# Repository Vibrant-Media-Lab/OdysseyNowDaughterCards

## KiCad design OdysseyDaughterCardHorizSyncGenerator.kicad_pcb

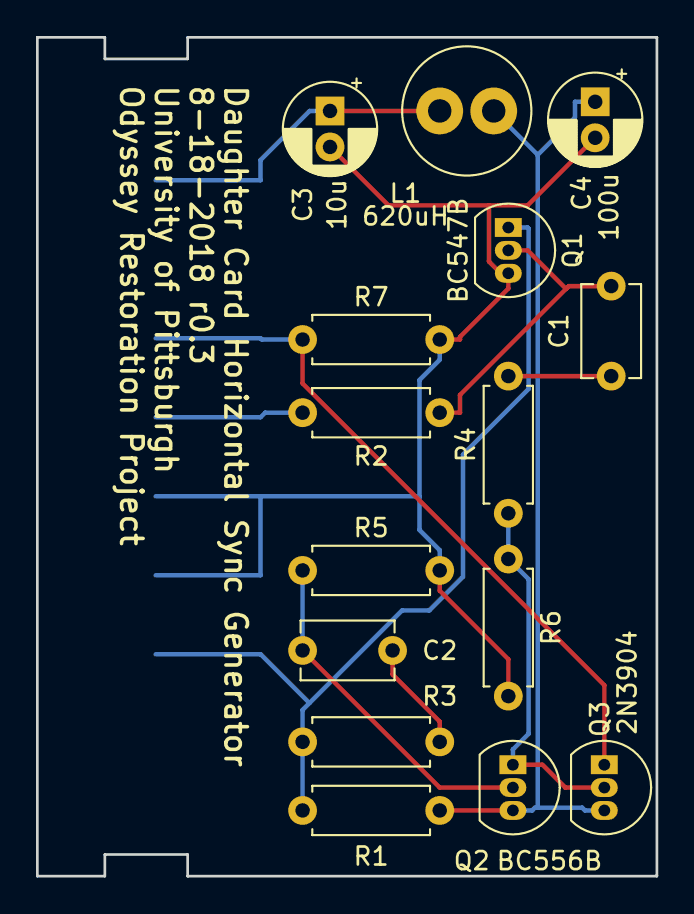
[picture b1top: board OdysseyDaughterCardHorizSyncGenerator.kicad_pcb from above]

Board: 2 copper layers, 34.4 x 46.6 mm, 16 parts (0 on the bottom side), 11 nets.

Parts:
C1: 470p; C_Disc_D5.1mm_W3.2mm_P5.00mm
C2: 680p; C_Disc_D5.1mm_W3.2mm_P5.00mm
C3: 10u; CP_Radial_D5.0mm_P2.00mm
C4: 100u; CP_Radial_D5.0mm_P2.00mm
L1: 620uH; L_Radial_D7.0mm_P3.00mm
Q1: BC547B; TO-92_Inline
Q2: BC556B; TO-92_Inline
Q3: 2N3904; TO-92_Inline
R1, R6: 1k; R_Axial_DIN0207_L6.3mm_D2.5mm_P7.62mm_Horizontal
R2: 150k; R_Axial_DIN0207_L6.3mm_D2.5mm_P7.62mm_Horizontal
R3: 820; R_Axial_DIN0207_L6.3mm_D2.5mm_P7.62mm_Horizontal
R4: 3.3k; R_Axial_DIN0207_L6.3mm_D2.5mm_P7.62mm_Horizontal
R5: 300k; R_Axial_DIN0207_L6.3mm_D2.5mm_P7.62mm_Horizontal
R7: 470; R_Axial_DIN0207_L6.3mm_D2.5mm_P7.62mm_Horizontal
X1: OdysseyDaughterCard; Odyssey_Daughter_Card

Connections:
/Card3: Q1.1, R1.1, R3.1, X1.3
/Card6: R2.1, X1.6
/Card7: Q3.1, R7.1, X1.7
/Card9: C3.1, L1.1, X1.9
GND: C3.2, C4.2, Q1.3, R5.2, R6.2, R7.2, X1.4, X1.5
unnamed: C1.1, R4.2
unnamed: C1.2, Q1.2, R2.2
unnamed: C2.1, Q2.2, R5.1
unnamed: C2.2, R3.2
unnamed: C4.1, L1.2, Q2.3, Q3.3, R1.2
unnamed: Q2.1, Q3.2, R4.1, R6.1

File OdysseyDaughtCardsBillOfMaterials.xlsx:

|  |  |  |  |  | # Parts | 19 | 12 | 15 | 19 | 15 | 11
 |  |  |  |  |  | Non PCB Cost Per Unit (10pcs) | 1.6139999999999999 | 2.2650000000000001 | 1.635 | 2.0720000000000001 | 2.0720000000000001 | 1.175
 |  |  |  |  |  | Non PCB Cost Per Unit (100pcs) | 0.8073999999999999 | 1.1888999999999998 | 0.79349999999999987 | 1.0053000000000001 | 1.0926 | 0.54569999999999996
Type | Value | P/N | Link | Notes | CPU (10pcs) | CPU (100pcs) (prices are from 2019) | Flip Flop | Gate Matrix | Horiz Sync Generator | Spot Gen | Summer | Vert Sync Generator
Capacitor | 0.01u | BC2662CT-ND | https://www.digikey.com/product-detail/en/vishay-bc-componen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 |  | 0.11799999999999999 | 5.9900000000000002E-2 |  |  |  | 1
Capacitor | 0.15u | 445-173584-1-ND | https://www.digikey.com/product-detail/en/tdk-corporation/FG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 |  | 0.18 | 0.1021 |  |  |  | 1
Capacitor | 0.1u | BC2665CT-ND | https://www.digikey.com/product-detail/en/vishay-bc-componen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 |  | 0.16 | 8.09E-2 | 2 |  |  | 1 |  | 2
Capacitor | 100p | BC2657CT-ND | https://www.digikey.com/product-detail/en/vishay-bc-componen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 |  | 0.122 | 6.2100000000000002E-2 | 2
Capacitor | 100u | 399-6602-ND | https://www.digikey.com/product-detail/en/kemet/ESK107M6R3AC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 |  | 0.114 | 5.3400000000000003E-2 |  |  | 1
Capacitor | 10u | 399-6597-ND | https://www.digikey.com/product-detail/en/kemet/ESK106M016AC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 |  | 0.105 | 4.9299999999999997E-2 |  |  | 1
Capacitor | 120p | BC2669CT-ND | https://www.digikey.com/product-detail/en/vishay-bc-componen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 |  | 0.12 | 6.08E-2 |  |  |  | 1
Capacitor | 1500p | 445-173589-1-ND | https://www.digikey.com/product-detail/en/tdk-corporation/FG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 |  | 0.18 | 0.1021 |  |  |  | 1
Capacitor | 470p | BC2681CT-ND | https://www.digikey.com/product-detail/en/vishay-bc-componen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 |  | 0.12 | 6.08E-2 |  |  | 1
Capacitor | 680p | BC2690CT-ND | https://www.digikey.com/product-detail/en/vishay-bc-componen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 |  | 0.123 | 6.25E-2 |  |  | 1
Diode | 1N4448 | 1N4448FS-ND | https://www.digikey.com/product-detail/en/on-semiconductor/1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 |  | 8.6999999999999994E-2 | 4.7300000000000002E-2 |  | 3 |  | 2 | 8
Diode | BAT83S | BAT83S-TRGICT-ND | https://www.digikey.com/product-detail/en/vishay-semiconduct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 |  | 0.314 | 0.16639999999999999 |  | 6 |  |  | 4
Inductor | 620uH 9 Ohm | RLB0608-681KL-ND | https://www.digikey.com/product-detail/en/bourns-inc/RLB0608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 |  | 0.314 | 0.16639999999999999 |  |  | 1
Resistor | 470 | CF14JT470RCT-ND | https://www.digikey.com/product-detail/en/stackpole-electron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 |  | 0.04 | 1.6199999999999999E-2 |  |  | 1 |  |  | 2
Resistor | 820 | CF14JT820RCT-ND | https://www.digikey.com/product-detail/en/stackpole-electron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 |  | 0.04 | 1.6199999999999999E-2 |  |  | 1 |  | 1 | 1
Resistor | 100k | CF14JT100KCT-ND | https://www.digikey.com/product-detail/en/stackpole-electron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 |  | 0.04 | 1.6199999999999999E-2 |  |  |  | 1
Resistor | 10k | CF14JT10K0CT-ND | https://www.digikey.com/product-detail/en/stackpole-electron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 |  | 0.04 | 1.6199999999999999E-2 |  |  |  | 5
Resistor | 150k | CF14JT150KCT-ND | https://www.digikey.com/product-detail/en/stackpole-electron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 |  | 0.04 | 1.6199999999999999E-2 |  |  | 1
Resistor | 180k | CF14JT180KCT-ND | https://www.digikey.com/products/en?keywords=CF14JT180KCT-ND |  | 0.04 | 1.6199999999999999E-2 |  |  |  |  |  | 1
Resistor | 18k | CF14JT18K0CT-ND | https://www.digikey.com/product-detail/en/stackpole-electron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 |  | 0.04 | 1.6199999999999999E-2 |  |  |  |  | 1
Resistor | 1k | CF14JT1K00CT-ND | https://www.digikey.com/product-detail/en/stackpole-electron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 |  | 0.04 | 1.6199999999999999E-2 | 2 |  | 2
Resistor | 2.2k | CF14JT2K20CT-ND | https://www.digikey.com/product-detail/en/stackpole-electron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 |  | 0.04 | 1.6199999999999999E-2 | 1 |  |  | 1 |  | 1
Resistor | 270k | CF14JT270KCT-ND | https://www.digikey.com/product-detail/en/stackpole-electron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 |  | 0.04 | 1.6199999999999999E-2 |  |  |  | 1
Resistor | 27k | CF14JT27K0CT-ND | https://www.digikey.com/product-detail/en/stackpole-electron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 |  | 0.04 | 1.6199999999999999E-2 |  |  |  |  | 1
Resistor | 3.3k | CF14JT3K30CT-ND | https://www.digikey.com/product-detail/en/stackpole-electron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 |  | 0.04 | 1.6199999999999999E-2 |  |  | 1
Resistor | 300k | CF14JT300KCT-ND | https://www.digikey.com/product-detail/en/stackpole-electron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 |  | 0.04 | 1.6199999999999999E-2 |  |  | 1 |  |  | 1
Resistor | 4.7k | CF14JT4K70CT-ND | https://www.digikey.com/product-detail/en/stackpole-electron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 |  | 0.04 | 1.6199999999999999E-2 |  | 3
Resistor | 47k | CF14JT47K0CT-ND | https://www.digikey.com/product-detail/en/stackpole-electron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 |  | 0.04 | 1.6199999999999999E-2 | 4
Switch/Button | Slide Switch SPDT Through Hole, Right Angle | CKN9559-ND | https://www.digikey.com/product-detail/en/c-k/OS102011MA1QN1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 |  |  |  | 4
Transistor | 2N3904 | 2N3904FS-ND | https://www.digikey.com/product-detail/en/on-semiconductor/2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 |  | 0.21 | 9.1600000000000001E-2 |  |  | 1 | 3 |  | 2
Transistor | 2N3906 | 2N3906TARFSCT-ND | https://www.digikey.com/product-detail/en/on-semiconductor/2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 |  | 0.19500000000000001 | 0.10349999999999999 | 2 |  |  |  |  | 1
Transistor | BC547B | BC547BTACT-ND | https://www.digikey.com/product-detail/en/on-semiconductor/B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 |  | 0.18099999999999999 | 9.6199999999999994E-2 |  |  | 1
Transistor | BC547C | BC547CBU-ND | https://www.digikey.com/product-detail/en/on-semiconductor/B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 |  | 0.19 | 0.10050000000000001 | 2 |  |  | 1
Transistor | BC556B | BC556BTACT-ND | https://www.digikey.com/product-detail/en/on-semiconductor/B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 |  | 0.188 | 9.9900000000000003E-2 |  |  | 1

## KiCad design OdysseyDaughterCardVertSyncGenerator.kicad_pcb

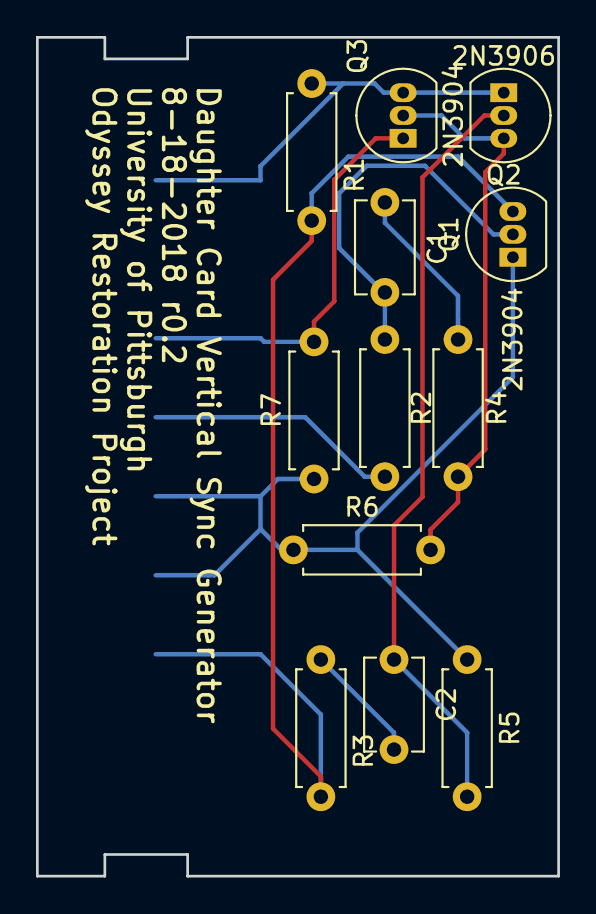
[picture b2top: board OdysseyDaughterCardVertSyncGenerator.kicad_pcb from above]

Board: 2 copper layers, 29.0 x 46.6 mm, 13 parts (0 on the bottom side), 10 nets.

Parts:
C1, C2: 0.1u; C_Disc_D5.1mm_W3.2mm_P5.00mm
Q1, Q3: 2N3904; TO-92_Inline
Q2: 2N3906; TO-92_Inline
R1, R6: 2.2k; R_Axial_DIN0207_L6.3mm_D2.5mm_P7.62mm_Horizontal
R2: 180k; R_Axial_DIN0207_L6.3mm_D2.5mm_P7.62mm_Horizontal
R3, R7: 470; R_Axial_DIN0207_L6.3mm_D2.5mm_P7.62mm_Horizontal
R4: 820; R_Axial_DIN0207_L6.3mm_D2.5mm_P7.62mm_Horizontal
R5: 300k; R_Axial_DIN0207_L6.3mm_D2.5mm_P7.62mm_Horizontal
X1: OdysseyDaughterCard; Odyssey_Daughter_Card

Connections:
/Card3: Q1.3, R1.2, R3.2, X1.3
/Card6: R2.2, X1.6
/Card7: Q3.1, R7.2, X1.7
/Card9: Q2.1, Q3.3, R1.1, X1.9
GND: Q1.1, R5.1, R6.1, R7.1, X1.4, X1.5
unnamed: C1.1, R4.2
unnamed: C1.2, Q1.2, R2.1
unnamed: C2.1, Q2.2, R5.2
unnamed: C2.2, R3.1
unnamed: Q2.3, Q3.2, R4.1, R6.2
